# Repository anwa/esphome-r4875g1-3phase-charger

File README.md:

# 3-Phase Huawei R4875G1 Battery Charger Controller

ESPHome-based controller for three Huawei R4875G1 rectifiers operated as a coordinated three-phase battery charger with a common parallel DC output.

<p align="center"><em>Shared V6 Dashboard running on the Charger Controller.</em></p>

The V6 firmware generation uses two coordinated targets based on the **Waveshare ESP32-S3-Touch-LCD-7**:

- the Charger Controller, physically attached to the rectifiers and responsible for CAN, charger control, safety and local blackstart
- the Remote HMI, which uses the same shared Dashboard, Rectifiers, Battery, System, Cooling and Trends presentation while receiving authoritative charger state and sending HMI command requests through Home Assistant

Remote HMI charger commands use Home Assistant transport and remain subject to authoritative validation and execution by the Charger Controller.

A Remote HMI is paired with a Charger Controller through one configurable Home Assistant entity prefix. The individual Dashboard telemetry, setpoint and command entity IDs are derived from that prefix, so pairing another charger does not require editing every Home Assistant entity mapping.

The Charger Controller currently provides:

- local charger control
- CAN communication with three independent R4875G1 rectifiers
- automatic discovery and reconnect handling
- capability-aware current limiting
- thermal protection and derating
- network-independent local blackstart operation
- a 7-inch LVGL touchscreen interface
- a direct-GPIO backup rotary encoder for network-independent setpoint and charger power control
- external compartment cooling
- controller backup-battery monitoring
- Home Assistant solar-battery-bank monitoring
- Home Assistant, MQTT and ESPHome web integration

The charger core is intentionally designed to remain operational without Wi-Fi, Home Assistant, MQTT or Internet access.

For detailed runtime and state-machine behavior, see [`R4875G1_CONTROL_FLOWS.md`](R4875G1_CONTROL_FLOWS.md).

For package ownership and firmware architecture, see [`packages/README.md`](packages/README.md).

Repository development rules are defined in [`AGENTS.md`](AGENTS.md) and the [`rules/`](rules/) directory.

> [!WARNING]
> This project controls equipment connected to mains voltage and a high-current
> DC battery bus.
>
> Three Huawei R4875G1 rectifiers can represent roughly 12 kW of charging power
> and more than 200 A on a 48–58 V DC bus.
>
> Firmware is not a substitute for correctly designed fuses, breakers,
> disconnects, BMS protection, earthing, isolation, conductor sizing and other
> required electrical safety measures.

---

## System Architecture

The intended installation uses one rectifier per AC phase while all three DC outputs feed the same battery/DC bus.

```text
Three-phase AC
    │
    ├── L1 -> R4875G1 Unit 1 ──┐
    ├── L2 -> R4875G1 Unit 2 ──┼── Common DC bus / battery
    └── L3 -> R4875G1 Unit 3 ──┘
                 │
                 └── Shared CAN bus
                          │
                          ▼
              Waveshare ESP32-S3 Controller
```

All rectifiers use:

```text
CAN bit rate:       125 kbit/s
CAN identifiers:    29-bit extended
DC voltage command: shared
DC current command: common per-unit request
```

Each rectifier maintains its own communication, lifecycle, discovery, thermal and telemetry state.

---

## V6 Hardware Targets

The current firmware targets:

```text
Waveshare ESP32-S3-Touch-LCD-7
ESP32-S3 N16R8
16 MB Flash
8 MB PSRAM
7-inch 800 × 480 RGB LCD
GT911 capacitive touchscreen
CH422G onboard I/O expander
onboard CAN transceiver
```

The controller uses the onboard ESP32-S3 TWAI peripheral and CAN transceiver.
No external SN65HVD230 module is required by the V6 hardware.

### External I2C Architecture

The shared controller I2C bus uses:

```text
GPIO8  -> SDA
GPIO9  -> SCL
400 kHz
```

External I2C peripherals use a dedicated second physical I2C bus. This isolates their addresses from the Waveshare onboard CH422G and allows the onboard display/touch bus to remain at 400 kHz.

```text
ESP32-S3
│
├── Onboard I2C — GPIO8 / GPIO9 — 400 kHz
│   ├── CH422G
│   └── GT911 touchscreen
│
└── External I2C — GPIO44 / GPIO43
    ├── MCP23017 @ 0x20
    │   ├── GPA0 -> external fan power enable
    │   ├── GPA1 -> Cooling Fan 1 tachometer
    │   └── GPA2 -> Cooling Fan 2 tachometer
    ├── BME280 @ 0x76
    │   ├── rectifier-compartment temperature
    │   ├── rectifier-compartment humidity
    │   └── station pressure
    └── EMC2101 @ 0x4C
        ├── external fan PWM
        └── Cooling Fan 3 tachometer
```

The MCP23017 is used without a dedicated ESP32 interrupt line; INTA and INTB are intentionally left unconnected.

The backup rotary encoder is connected directly to the ESP32-S3 rather than through I2C:

```text
GPIO11 -> Encoder S1 / A
GPIO12 -> Encoder S2 / B
GPIO13 -> Encoder KEY
```

GPIO11, GPIO12 and GPIO13 are the Waveshare TF-card SPI pins, so the TF-card interface is unavailable while the backup encoder uses them.

The BME280 station pressure is exposed directly. A second pressure entity publishes the standard-atmosphere sea-level equivalent for the fixed 316 m installation altitude.

Unused MCP23017 pins remain available for future expansion.

---

## CAN Communication

The three Huawei rectifiers share one CAN bus.

The firmware implements independent per-unit communication state and explicit rectifier lifecycle handling:

```text
OFFLINE
   │
   │ CAN communication detected
   ▼
DISCOVERING
   │
   │ required discovery completed
   │ active setpoints restored
   ▼
ONLINE
```

A rectifier that loses valid communication returns to `OFFLINE`.

Normal high-rate telemetry polling is restricted to `ONLINE` units.

`OFFLINE` units are probed at a much lower rate using single-shot CAN transmission so an absent rectifier cannot continuously force the ESP32 TWAI controller toward `BUS_OFF`.

The firmware also implements explicit TWAI recovery if the complete physical CAN network disappears.

### Discovery

Discovery retrieves information including:

- static rectifier identification properties
- maximum DC-current capability
- shelf/address information

Discovery traffic is serialized so only one discovery operation owns the CAN bus at a time.

A successfully rediscovered unit receives the currently active DC voltage and current commands before its lifecycle returns to `ONLINE`.

---

## Charger Control

The controller manages three rectifiers as one coordinated charger while preserving independent per-unit safety and communication state.

Supported charger-wide controls include:

```text
Active DC voltage
Active per-unit DC current
Nominal three-unit DC power target
START
STOP
Fallback DC voltage
Fallback DC current
```

The nominal DC power target is converted into a common per-unit current request.

The requested current and the actually applied current are intentionally kept separate.

The final applied current is limited by:

```text
min(
    requested current,
    effective hardware capability,
    thermal current limit
)
```

This allows the requested charger target to remain unchanged while hardware or thermal protection temporarily reduces the current actually sent to the rectifiers.

---

## Capability-Aware Current Limiting

R4875G1 variants can report different maximum-current capabilities.

The controller therefore discovers the capability of each reachable unit and derives a safe shared limit.

The basic policy is:

```text
No reachable rectifier
    -> conservative fail-safe current ceiling

Reachable rectifier with unknown capability
    -> conservative fail-safe current ceiling

All reachable capabilities known
    -> effective ceiling = lowest reachable capability
```

Command scaling is derived independently from the detected rectifier capabilities so mixed-capability installations remain fail-safe.

A diagnostic entity reports capability mismatches between simultaneously reachable rectifiers.

---

## Thermal Protection

Each rectifier has an independent thermal state:

```text
NORMAL
WARNING_1
WARNING_2
LOCKOUT
```

The current configuration uses staged derating:

```text
70 °C -> first warning / reduced current
80 °C -> stronger current reduction
90 °C -> individual overtemperature shutdown
```

Hysteresis prevents rapid state oscillation while temperatures fall.

A thermal lockout is not cleared by missing or stale telemetry. Valid temperature data must confirm that the rectifier has returned to a safe temperature.

The shared thermal current ceiling is derived from the most restrictive active per-unit thermal state.

---

## Local Blackstart

Core charger operation is designed to remain available without network services.

Blackstart does not depend on:

```text
Home Assistant
MQTT
Wi-Fi
Internet access
```

Before a rectifier receives a START command, the controller verifies that it:

```text
is lifecycle ONLINE
has fresh CAN communication
reports explicit power state OFF
has valid output-temperature telemetry
is below the configured overtemperature trip threshold
has no active overtemperature lockout
```

Only units passing all checks receive the ON command.

STOP remains unrestricted.

This allows a partially available charger to remain controllable while preventing unknown or unsafe units from being started.

---

## Local User Interface

The controller uses the Waveshare 7-inch 800 × 480 RGB display with GT911 capacitive touch.

The display backlight is automatically disabled after the target-specific LVGL idle timeout while charger control and telemetry continue running normally. Touching and releasing the sleeping touchscreen always wakes the display without activating the control underneath the wake-up touch.

Each V6 target may optionally import its own Home Assistant occupancy/motion entity. Active motion wakes the display immediately and keeps the existing LVGL inactivity timer alive. When motion ends, the same configured idle timeout starts again. If no motion package is composed for a target, the original touch and idle-timeout behavior is unchanged. Home Assistant `unknown`, `unavailable` or connection loss is treated as no motion.

The LVGL interface contains six primary functional pages:

```text
Dashboard
Rectifiers
Battery
System
Cooling
Trends
```

The Rectifiers page also provides one shared hierarchical detail view for Units 1, 2 and 3.

### Dashboard

The Dashboard uses four equal-width overview cards for AC input, DC output, charger state and the external solar battery bank.

It provides charger-wide operating information including:

```text
AC input power
AC voltage
AC current
AC current limit
DC output power
DC voltage
combined DC current
active DC voltage limit
nominal total DC power target
available rectifier count
running rectifier count
highest rectifier output temperature
conversion efficiency
charger START/STOP state
solar battery-bank SOC
solar battery-bank power
solar battery-bank voltage
solar battery-bank current
solar battery-bank temperature
solar battery-bank operating state
```

AC and DC setpoints are edited through dedicated modal dialogs opened from the corresponding Dashboard cards.

Solar battery-bank information is imported from Home Assistant for monitoring only. Missing Home Assistant battery telemetry is shown explicitly and does not affect charger control or safety behavior.

### Rectifiers

The Rectifiers page provides one overview card for each unit.

Each rectifier maintains independent:

```text
lifecycle state
power state
CAN state
AC telemetry
DC telemetry
temperature
internal fan telemetry
```

Selecting a unit opens the shared Rectifier Detail page.

### Rectifier Detail

The detail view exposes extended per-unit information including:

```text
AC voltage
AC current
AC power
AC frequency
DC voltage
DC current
DC power
input temperature
output temperature
internal fan RPM
internal fan target duty
internal fan minimum duty
maximum-current capability
operating hours
fallback voltage
fallback current
```

One LVGL page is reused dynamically for all three rectifiers.

### Battery

The Battery page provides one monitoring card for each of four parallel solar-battery units. The same page layout and runtime are used by the Charger Controller and Remote HMI through the shared Battery UI model.

Each card displays:

```text
voltage
current
power
state of charge
temperature
cell drift
warning state
fault state
```

A consolidated per-battery status shows:

```text
HA OFFLINE
NO DATA
OK
WARNING
FAULT
```

`HA OFFLINE` indicates that no Home Assistant state-subscription connection is available.
`NO DATA` indicates that Home Assistant is connected but one or more required battery entities are unavailable or invalid.

Fault has priority over warning. Missing or invalid Home Assistant data is displayed explicitly instead of being treated as a healthy battery state.

All solar-battery telemetry is monitoring-only. It does not participate in charger setpoint calculation, START eligibility, thermal protection, CAN control or other charger safety decisions.

### Cooling

The Cooling page displays the shared rear-compartment environmental data and internal rectifier-fan telemetry.

External chassis-fan control is implemented independently by `packages/cooling.yaml`.

### System

The System page is shared by the Charger Controller and Remote HMI. It combines diagnostics measured locally on the active display controller with authoritative rectifier lifecycle state from the shared UI model.

```text
local network state
local Wi-Fi signal
local uptime
local CPU temperature
local memory/runtime information
local backup-battery voltage and state of charge
rectifier lifecycle status
```

On the Remote HMI, local device diagnostics remain available independently of Home Assistant. Rectifier state still follows the Charger Controller through Home Assistant and the shared UI-model boundary.

### Trends

Five independent sixty-minute ring buffers are maintained continuously:

```text
Combined DC Power
Combined DC Current
Average DC Voltage
Highest Rectifier Output Temperature
Rectifier Compartment Temperature
```

Sampling uses:

```text
10-second interval
360 samples
60-minute history
```

The chart time axis uses ten-minute divisions labeled from `-60 min` through `-10 min` and `now`.

Combined DC current and average DC voltage share one dual-axis chart. Current uses the left Y axis in amperes and voltage uses the right Y axis in volts, while both series use the same sixty-minute time base.

Invalid source values are preserved as gaps instead of being converted to artificial zero values.

---

## Backup Rotary Encoder and Blackstart Control

The Charger Controller uses a mechanical rotary encoder connected directly to ESP32-S3 GPIOs:

```text
GPIO11 -> Encoder S1 / A
GPIO12 -> Encoder S2 / B
GPIO13 -> Encoder KEY
```

The native ESPHome `rotary_encoder` component decodes the two quadrature channels with one output step per complete quadrature cycle. The physical encoder direction is mapped so clockwise rotation increases the active edit value.

The backup interaction is intentionally independent from normal touchscreen navigation:

```text
short press 1 -> edit charger-wide DC voltage
rotation      -> adjust voltage in 0.1 V steps
short press 2 -> edit nominal DC sum power
rotation      -> adjust power in 0.1 kW steps
short press 3 -> apply both pending setpoints

long press while idle -> request charger START or STOP
15 s inactivity       -> discard pending edits
```

Setpoint saves and charger power requests reuse the authoritative Charger Controller command paths. The encoder does not implement separate CAN or safety logic, and normal START eligibility remains authoritative.

The Controller-only LVGL overlay provides visual feedback while the display is available, but the encoder state machine and charger command path do not depend on touchscreen input, Home Assistant, MQTT or Internet access.

---

## External Cooling System

The external chassis cooling system is independent of the internal fans built into the Huawei rectifiers.

Three external fans are supported.

```text
MCP23017 GPA0 -> common fan-supply enable
MCP23017 GPA1 -> Fan 1 tachometer
MCP23017 GPA2 -> Fan 2 tachometer

EMC2101 PWM   -> common four-pin fan PWM
EMC2101 TACH  -> Fan 3 tachometer
```

Every fan retains its own tachometer signal.

The EMC2101 generates the shared hardware PWM signal at approximately:

```text
25.7 kHz
```

Cooling Fan 3 ventilates the rear rectifier compartment where the BME280 temperature/humidity/pressure sensor is installed.

### Web Controls and EMC2101 Telemetry

The ESPHome Web UI exposes the external cooling controls and EMC2101 telemetry:

```text
Cooling Fan Automatic
Cooling Fan Power
Cooling Fan Manual PWM
Cooling Fan PWM Actual
Cooling Fan Controller Temperature
Cooling Fan 1 RPM
Cooling Fan 2 RPM
Cooling Fan 3 RPM
```

`Cooling Fan Controller Temperature` reports the EMC2101 internal chip temperature. `Cooling Fan PWM Actual` reports the PWM duty cycle read back from the EMC2101 controller; it represents the programmed hardware setting rather than an independent measurement of the electrical PWM waveform.

Automatic and manual PWM control maintain separate state. While `Cooling Fan Automatic` is enabled, the compartment-temperature controller drives the EMC2101 PWM output directly and the manual PWM value remains stored without affecting the active output. When automatic mode is disabled, the stored `Cooling Fan Manual PWM` value is applied immediately and subsequent slider changes control the PWM output directly.

`Cooling Fan Power` controls the common external fan supply independently and remains available for manual operation when automatic mode is disabled.

### Automatic Cooling

Automatic cooling is enabled by default.

The current temperature curve is:

| Compartment temperature | Fan command |
| --- | ---: |
| `< 30 °C` | OFF / 0 % |
| `30–34.9 °C` | 35 % |
| `35–39.9 °C` | 45 % |
| `40–44.9 °C` | 60 % |
| `45–49.9 °C` | 80 % |
| `>= 50 °C` | 100 % |

Downward transitions use hysteresis.

If compartment-temperature telemetry becomes unavailable, the cooling system fails safe by enabling the external fans at 100 %.

---

## Local Display Backup Battery

Both V6 Waveshare display controllers support a local 1S lithium backup battery through the J3 battery connector.

The board provides an existing divider:

```text
VBAT -> 200 kΩ -> TP1 -> 100 kΩ -> GND
```

TP1 is externally connected to:

```text
J8 pin 3 / AD -> GPIO6
```

The ADC therefore sees one third of the battery voltage and the firmware restores the actual value using a factor of 3.

The measured voltage is filtered and exposed with a target-specific name:

```text
Controller Battery Voltage
Remote HMI Battery Voltage
```

A second sensor derives an approximate voltage-based state of charge:

```text
Controller Battery State of Charge
Remote HMI Battery State of Charge
```

The SOC value is intended for monitoring only. It is not a replacement for coulomb counting or a dedicated fuel-gauge IC.

---

## Solar Battery Bank Monitoring

Both V6 targets import monitoring data for an external four-unit solar battery bank from Home Assistant through the ESPHome native API.

All configurable Home Assistant entity mappings are centralized in:

```text
packages/shared/battery-bank.yaml
```

The imported aggregate bank data includes:

```text
voltage
current
power
state of charge
temperature
operating state
```

Each of the four individual battery units provides:

```text
voltage
current
power
state of charge
temperature
cell drift
warning state
fault state
```

The Home Assistant battery-bank and individual battery power entities are normalized internally from watts to kilowatts.

Battery warning and fault entities are imported as text states so `on`, `off`, `unknown` and `unavailable` remain distinguishable. After source validation, the shared Battery UI backend normalizes valid warning and fault states to boolean values in the target-neutral UI model.

Home Assistant battery telemetry is intentionally isolated from charger control. The charger remains locally operational when Wi-Fi or Home Assistant is unavailable.

---

## Network Interfaces

Network services provide additional monitoring and control but are not part of the local charger safety path.

The firmware integrates:

```text
ESPHome native API
MQTT
ESPHome Web Server
OTA
SNTP time synchronization
```

Home Assistant can therefore expose charger telemetry, diagnostics, setpoints and control entities while local operation remains independent.

---

## Firmware Architecture

The V6 generation is assembled from two root configurations plus shared and target-specific ESPHome packages.

```text
r4875g1-3phase-charger.yaml
r4875g1-remote-hmi.yaml
trend_helpers.h

packages/
├── version.yaml
├── controls.yaml
├── cooling.yaml
├── display.yaml
├── rectifier-shared.yaml
├── rectifier-unit.yaml
│
├── shared/
│   ├── core.yaml
│   ├── hardware.yaml
│   ├── local-diagnostics.yaml
│   ├── ui-model.yaml
│   ├── ui-contract.yaml
│   └── battery-monitoring.yaml
│
├── controller/
│   ├── hardware.yaml
│   ├── mqtt.yaml
│   ├── ui-backend.yaml
│   ├── ui-rectifier-backend.yaml
│   └── ui-commands.yaml
│
├── remote-hmi/
│   ├── connection-status.yaml
│   ├── ha-entity-map.yaml
│   ├── ha-backend.yaml
│   ├── rectifier-backend.yaml
│   └── ui-commands.yaml
│
├── display/
│   ├── shared-hmi.yaml
│   ├── shared-dashboard.yaml
│   ├── shared-rectifiers.yaml
│   ├── shared-battery.yaml
│   ├── shared-system.yaml
│   ├── shared-cooling.yaml
│   ├── shared-trends.yaml
│   ├── shared-navigation.yaml
│   └── pages/
│
└── rectifier-can/
    └── parameterized CAN receive handlers
```

### Package Responsibilities

| Package | Responsibility |
| --- | --- |
| `version.yaml` | coordinated V6 firmware version source of truth |
| `shared/core.yaml` | shared ESP32 platform, network, API, web, OTA and time services |
| `shared/hardware.yaml` | shared Waveshare board peripherals and local backup-battery monitoring |
| `shared/ui-model.yaml` | target-neutral state consumed by the shared HMI |
| `shared/battery-monitoring.yaml` | shared Home Assistant solar-battery monitoring and UI-model backends |
| `controller/hardware.yaml` | Charger Controller CAN, external I2C and charger-side hardware |
| `controller/ui-backend.yaml` | publishes authoritative local charger state into the shared UI model |
| `controller/ui-commands.yaml` | executes shared HMI command intents on the Charger Controller |
| `remote-hmi/ha-backend.yaml` | imports authoritative Charger Controller state through Home Assistant |
| `remote-hmi/ui-commands.yaml` | transports shared HMI command intents through Home Assistant |
| `remote-hmi/connection-status.yaml` | persistent Remote HMI Home Assistant connectivity presentation |
| `controls.yaml` | charger-wide user setpoints and controls |
| `cooling.yaml` | Charger Controller external chassis-fan control and RPM monitoring |
| `display.yaml` | Charger Controller aggregation of the shared display packages |
| `display/shared-hmi.yaml` | shared display infrastructure, presentation state, header and local trend history |
| `display/shared-*.yaml` | shared page presentation/runtime compositions for both V6 targets |
| `display/shared-navigation.yaml` | shared six-page bottom navigation |
| `rectifier-shared.yaml` | shared lifecycle, safety, discovery, CAN scheduling and control |
| `rectifier-unit.yaml` | parameterized per-unit state and telemetry |
| `rectifier-can/*.yaml` | parameterized CAN receive handlers |
| `trend_helpers.h` | native LVGL chart declarations used by the shared Trends runtime |

The detailed ownership model is documented in [`packages/README.md`](packages/README.md).

---

## Display Architecture

Both V6 targets use the same shared LVGL presentation. Target-specific backends translate their native state into the shared UI model, and shared page runtimes consume only that target-neutral model.

```text
                         Shared LVGL HMI
                               │
                               ▼
                       Shared UI model
                               │
                ┌──────────────┴──────────────┐
                ▼                             ▼
      Charger Controller backend       Remote HMI backend
                │                             │
                ▼                             ▼
       Local runtime / CAN          Home Assistant entities
```

The shared display composition contains:

```text
shared-hmi
shared-dashboard
shared-rectifiers
shared-battery
shared-system
shared-cooling
shared-trends
shared-navigation
```

Only the currently visible page receives normal page-specific display refreshes. Persistent header state, command-transition state, local backup-battery presentation and local trend sampling continue independently on each target.

---

## Building

The two V6 ESPHome root configurations are:

```text
r4875g1-3phase-charger.yaml
r4875g1-remote-hmi.yaml
```

Validate and compile the Charger Controller with:

```bash
esphome config r4875g1-3phase-charger.yaml
esphome compile r4875g1-3phase-charger.yaml
```

Validate and compile the Remote HMI with:

```bash
esphome config r4875g1-remote-hmi.yaml
esphome compile r4875g1-remote-hmi.yaml
```

Changes to shared V6 HMI code or shared target contracts must be validated against both targets. Hardware-dependent behavior should also be tested on the affected physical target after successful compilation.

---

## Versioning

The firmware version has exactly one source of truth:

```text
packages/version.yaml
```

Do not duplicate the current firmware version in documentation.

Version changes follow:

```text
rules/versioning.md
```

Pure documentation and repository-cleanup changes do not require a firmware version increment unless they also change runtime behavior.

---

## Repository Development Rules

AI-assisted and human development follows the repository rules in:

```text
AGENTS.md
rules/
```

`AGENTS.md` is the entry point for agents.

All human-readable repository content created or substantially modified by the project is written in English.

The repository rules define:

```text
development workflow
Git workflow
versioning
documentation
YAML comment style
```

---

## V4 Hardware Variant

The previous ESP32-S3-DevKitC-1 hardware implementation remains maintained separately on:

```text
v4-maintenance
```

V4 is a permanent hardware variant rather than the active V6 controller target.

Changes that are genuinely shared between both hardware generations may be ported when appropriate, but V6-specific display, I/O and hardware assumptions must not be applied blindly to the V4 branch.

---

## Related Projects and References

The following projects and documentation were particularly useful during the development and verification of the R4875G1 Charger Controller:

- [CAN-BUS-control-R4875G1-with-ESPHome-and-MQTT](https://github.com/mjpalmowski/CAN-BUS-control-R4875G1-with-ESPHome-and-MQTT)
  This project originally grew from the Huawei R4875G1 CAN and ESPHome work published by **mjpalmowski**. It provided important groundwork for Huawei CAN protocol research, telemetry decoding, control commands, property and capability discovery, and ESPHome integration.

- [patagonaa/huawei-r48xx](https://github.com/patagonaa/huawei-r48xx)
  Extensive R48xx-series documentation covering connectors, mechanical models, CAN protocol details, register behavior, software-address negotiation and model-specific observations. Its 3D PSU and case models also provided useful reference geometry for the charger's mechanical enclosure development.

- [craigpeacock/Huawei_R4850G2_CAN](https://github.com/craigpeacock/Huawei_R4850G2_CAN)
  Earlier public CAN protocol research for Huawei R48xx rectifiers and an additional useful reference while validating protocol behavior.

The Controller implementation in this repository has since evolved into a dedicated three-unit charger with independent per-unit lifecycle management, local and network-independent control, automatic CAN recovery, capability-aware current limiting, thermal protection, local blackstart operation, a shared touchscreen HMI architecture and external cooling management.

The implementation is independently maintained and contains additional multi-rectifier lifecycle, reconnect, capability, thermal, blackstart and HMI behavior specific to this project.

---

## Disclaimer

This repository is provided for development and experimentation with Huawei R4875G1 rectifiers.

Anyone building or operating hardware based on this project is responsible for the electrical, thermal and mechanical safety of the resulting system.

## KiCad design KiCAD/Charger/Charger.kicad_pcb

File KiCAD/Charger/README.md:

# R4875G1 3-Phase Charger – V4 KiCad Hardware

This directory contains the KiCad schematic and PCB design for the V4 hardware generation of the R4875G1 three-phase charger controller.

> [!IMPORTANT]
> This KiCad project does **not** represent the current V6 Charger Controller hardware.
>
> The current V6 firmware targets the Waveshare ESP32-S3-Touch-LCD-7 and uses a substantially different display, CAN, backup-encoder and external-I/O architecture.
>
> The V4 hardware remains a maintained hardware variant on the `v4-maintenance` branch.

## V4 Controller Hardware

The V4 controller is based on an **Espressif ESP32-S3-DevKitC-1** fitted with an **ESP32-S3-WROOM-1-N16R8** module with 16 MB Flash and 8 MB PSRAM.

The KiCad schematic uses the `PCM_Espressif:ESP32-S3-DevKitC` symbol and footprint.

The design includes the hardware required by the V4 controller architecture, including the external display, CAN interface, rotary encoder and chassis-fan connections.

## V4 GPIO Map

The KiCad design uses the following V4 controller assignments:

| Function | GPIOs |
|---|---:|
| Encoder push button | 2 |
| TFT backlight PWM | 4 |
| TFT CS / RESET / DC | 5, 6, 7 |
| I2C SDA / SCL | 8, 9 |
| TFT SPI MOSI / MISO / CLK | 11, 12, 13 |
| CAN / TWAI TX / RX | 15, 16 |
| Rotary encoder A / B | 17, 18 |
| FAN_ENABLE | 21 |
| FAN3_TACH / FAN2_TACH / FAN1_TACH | 39, 40, 41 |
| FAN_PWM | 42 |

These assignments describe the V4 KiCad hardware and MUST NOT be used as the GPIO map for the current V6 firmware.

## V6 Charger Controller Hardware

The current V6 Charger Controller uses the **Waveshare ESP32-S3-Touch-LCD-7** as its hardware platform.

Important architectural differences include:

| Function | V4 KiCad hardware | V6 Charger Controller |
|---|---|---|
| Controller | ESP32-S3-DevKitC-1 | Waveshare ESP32-S3-Touch-LCD-7 |
| Display | External ILI9488 over SPI | Onboard 800×480 RGB LCD |
| Touch | None | GT911 capacitive touch |
| CAN | External CAN interface | Onboard CAN transceiver |
| Rotary encoder | Direct GPIO17 / GPIO18, button GPIO2 | Direct GPIO11 / GPIO12, button GPIO13 |
| External fan enable | Direct ESP32 GPIO | MCP23017 GPA0 |
| Fan 1 / Fan 2 tachometer | Direct ESP32 GPIOs | MCP23017 GPA1 / GPA2 |
| MCP23017 interrupt | Not used | INTA / INTB intentionally unconnected |
| Fan 3 tachometer | Direct ESP32 GPIO | EMC2101 |
| External fan PWM | ESP32 PWM | EMC2101 |
| External I2C bus | Shared main bus | Dedicated GPIO44 / GPIO43 bus |

The V6 hardware architecture is documented in the repository root `README.md` and `packages/README.md`.

A V6 KiCad design should be maintained as a separate hardware design rather than modifying this V4 project in place.

## Project Files

```text
Charger.kicad_pro
    KiCad project configuration

Charger.kicad_sch
    main V4 controller schematic

fan-control.kicad_sch
    external fan-control schematic

Charger.kicad_pcb
    V4 PCB layout
```

## External Libraries

The project uses symbols, footprints and/or 3D models from the official Espressif KiCad Libraries:

`https://github.com/espressif/kicad-libraries`

The Espressif KiCad Libraries are licensed separately under the **Creative Commons CC BY-SA 4.0 License with the exception stated by Espressif**. See the upstream repository for the complete license terms.

## License

The charger PCB design and project files in this repository are licensed under the **MIT License**, unless otherwise noted.

Third-party library files remain subject to their respective upstream licenses.

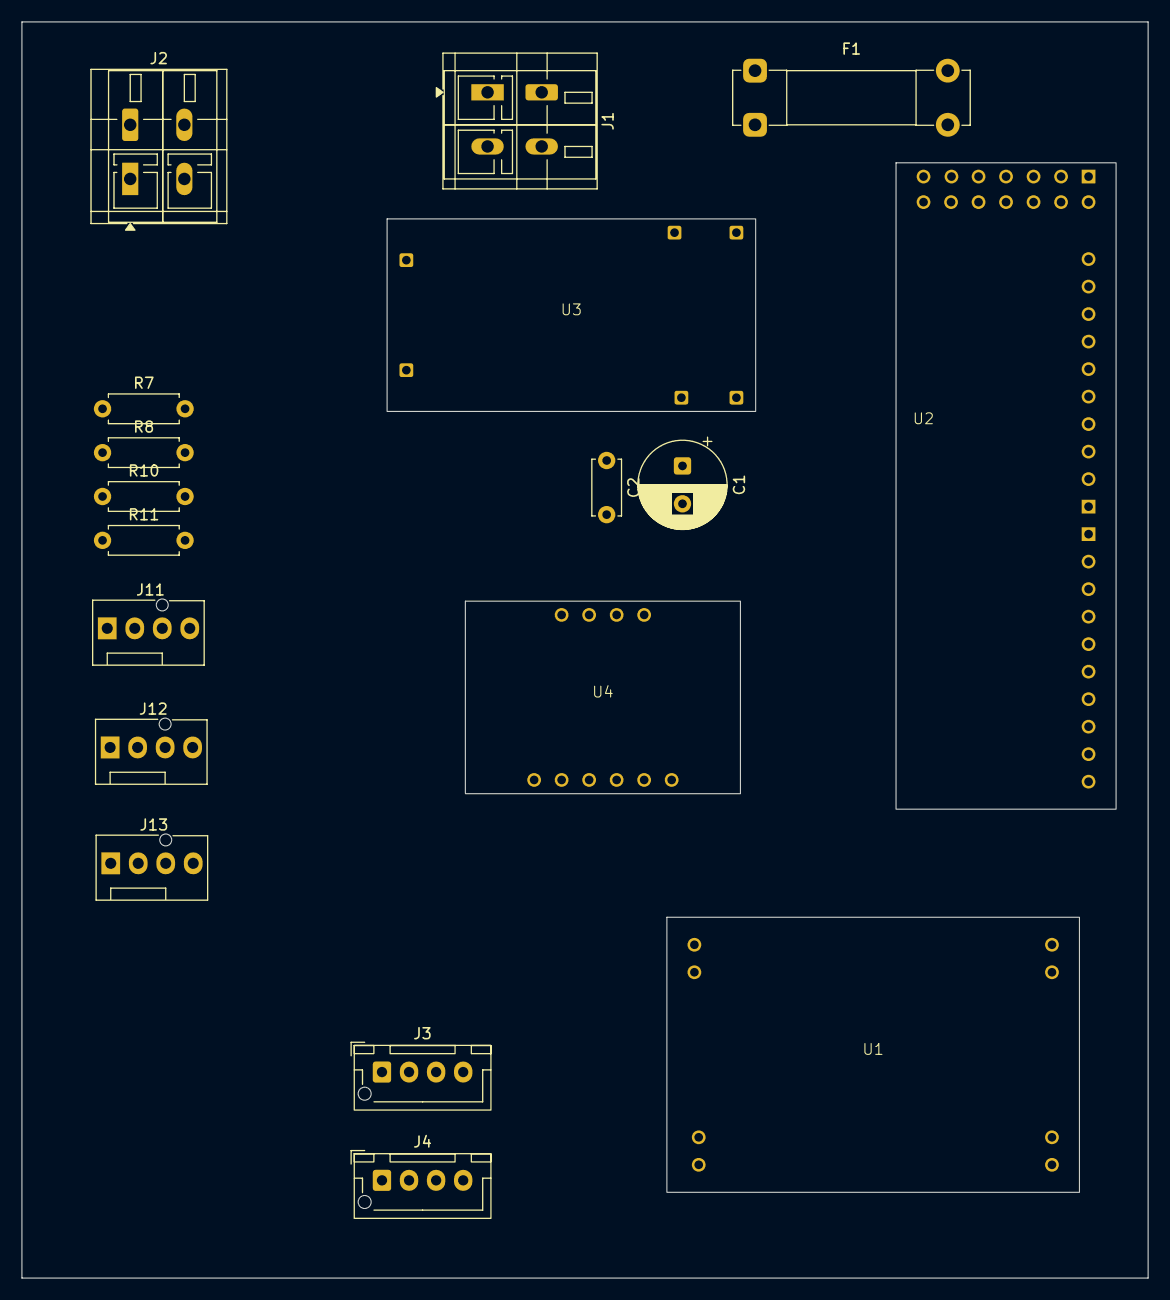
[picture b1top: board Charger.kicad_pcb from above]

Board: 2 copper layers, 104.0 x 116.0 mm, 18 parts (0 on the bottom side), 13 nets, no tracks yet.

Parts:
C1: 470uF; CP_Radial_D8.0mm_P3.50mm
C2: 100nF; C_Disc_D5.0mm_W2.5mm_P5.00mm
F1: Fuse_Small; Fuseholder_Clip-5x20mm_Bel_FC-203-22_Lateral_P17.80x5.00mm_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
J1, J2: Screw_Terminal_01x02; TerminalBlock_WAGO_236-402_1x02_P5.00mm_45Degree
J3, J4: Conn_01x04_Socket; JST_XH_B4B-XH-AM_1x04_P2.50mm_Vertical
J11, J12, J13: Conn_01x04; FanPinHeader_1x04_P2.54mm_Vertical
R7, R8: 10k; R_Axial_DIN0207_L6.3mm_D2.5mm_P7.62mm_Horizontal
R10, R11: 1k; R_Axial_DIN0207_L6.3mm_D2.5mm_P7.62mm_Horizontal
U1: DC-DC
U2: MCP23017
U3: MOSFET
U4: EMC2101

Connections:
+3.3V: J3.2, J4.2, R7.1, R8.1, U2.1 (VCC), U2.18 (VCC), U4.1 (VIN)
+12V: C1.1, C2.1, F1.2, U1.2 (IN+)
/FAN1_TACH: R10.1, U2.21 (PA1)
/FAN2_TACH: R11.1, U2.22 (PA2)
/FAN+: J11.2, J12.2, J13.2
/PWM: J11.4, J12.4, J13.4, U4.8 (FAN)
/SCl: J3.3, J4.3, U4.5 (SDA)
/SDA: J3.4, J4.4, U2.4 (SDA), U4.4 (SCL)
/TACH1: J11.3, R7.2, R10.2, U4.7 (TACH)
/TACH2: J12.3, R8.2, R11.2
GND: C1.2, C2.2, J1.2, J2.2, J3.1, J4.1, J11.1, J12.1, J13.1, U1.1 (IN-), U1.3 (OUT-), U2.2 (GND), U2.19 (GND), U3.2 (GND_2), U4.3 (GND)
unnamed: F1.1, J1.1
unnamed: J2.1, U1.4 (OUT+)
